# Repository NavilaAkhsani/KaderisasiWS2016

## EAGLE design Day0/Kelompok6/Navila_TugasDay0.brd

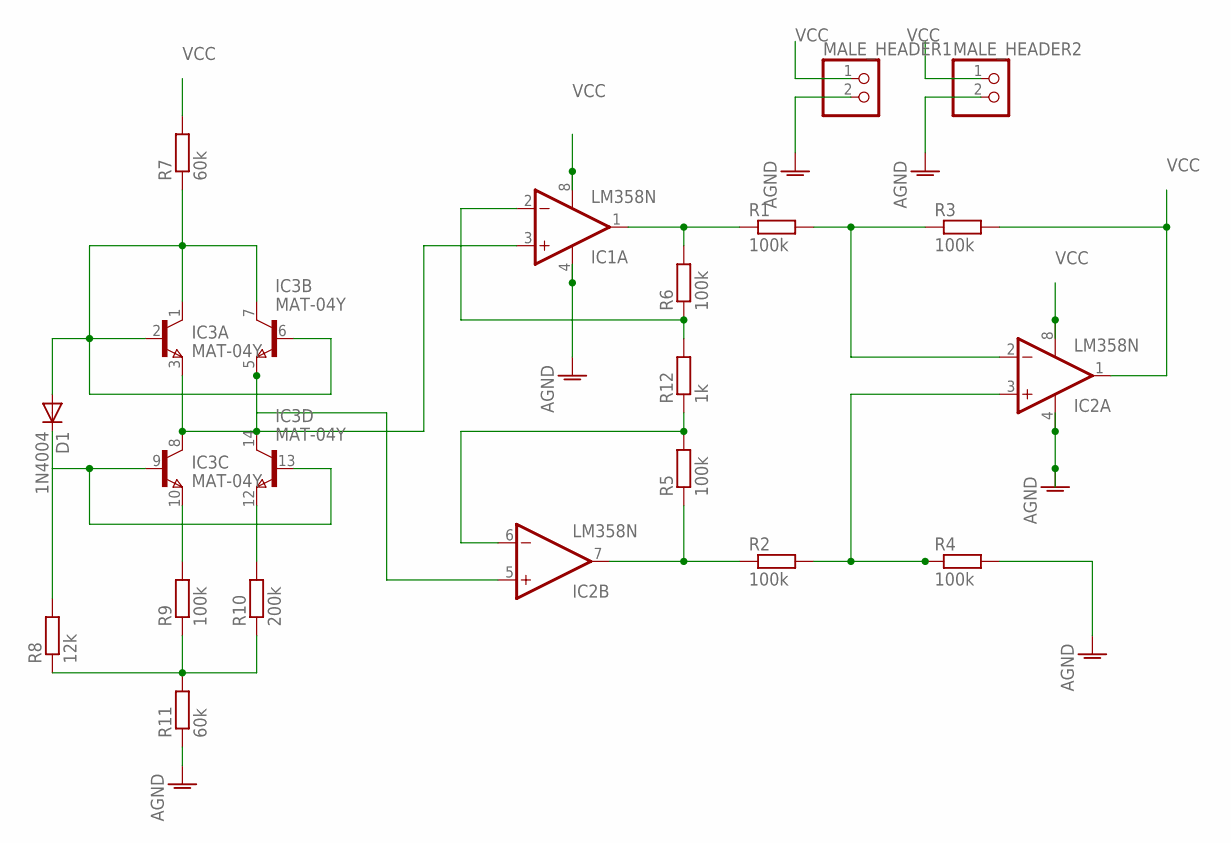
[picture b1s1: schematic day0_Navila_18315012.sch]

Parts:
D1: 1N4004; DO41-10
IC1, IC2: LM358N; DIL08
IC3: MAT-04Y; DIL14
MALE_HEADER1, MALE_HEADER2: PINHD-1X2; 1X02
R1, R2, R3, R4, R5, R6, R9: 100k; 0204/5
R7, R11: 60k; 0204/5
R8: 12k; 0204/5
R10: 200k; 0204/5
R12: 1k; 0204/5

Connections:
AGND: IC2.4 (V-), MALE_HEADER1.2, MALE_HEADER2.2
unnamed: D1.A, IC3.1 (C), IC3.2 (B), IC3.6 (B), IC3.7 (C), R7.1
unnamed: D1.C, IC3.9 (B), IC3.13 (B), R8.2
unnamed: R8.1, R9.1, R10.1, R11.2
unnamed: IC2.3 (+IN), R2.2, R4.1
unnamed: IC2.2 (-IN), R1.2, R3.1
unnamed: IC1.3 (+IN), IC2.5 (+IN), IC3.3 (E), IC3.5 (E), IC3.8 (C), IC3.14 (C)
unnamed: IC3.12 (E), R10.2
unnamed: IC3.10 (E), R9.2
unnamed: IC1.2 (-IN), R6.1, R12.2
unnamed: IC2.6 (-IN), R5.2, R12.1
unnamed: IC1.1 (OUT), R1.1, R6.2
unnamed: IC2.7 (OUT), R2.1, R5.1
VCC: IC1.8 (V+), IC2.1 (OUT), IC2.8 (V+), MALE_HEADER1.1, MALE_HEADER2.1, R3.2, R7.2

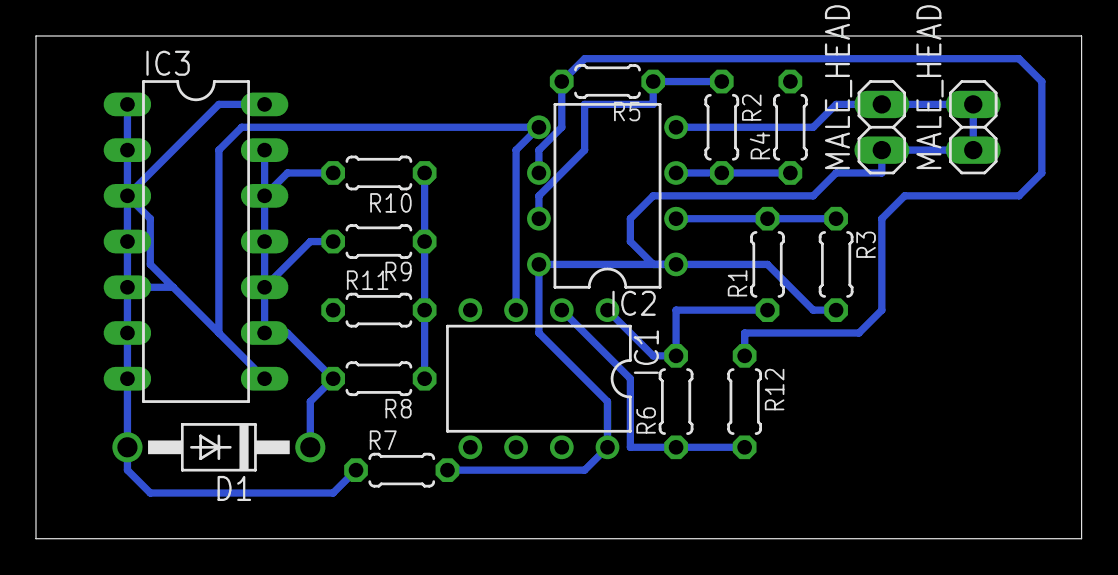
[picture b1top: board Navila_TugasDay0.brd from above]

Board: 2 copper layers, 58.1 x 27.9 mm, 18 parts (0 on the bottom side), 14 nets.
